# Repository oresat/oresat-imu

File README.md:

# oresat-imu
OreSat's IMU + Magnetometer board

CAN address: 0xh41

The IMU on the LV2 flight computer is the [ADIS16405](http://www.analog.com/en/products/sensors/inertial-measurement-units/adis16405.html#product-overview). The IMU contains a triaxial gyroscope, triaxial accelerometer, and an embedded temperature sensor. These parameters are output from the IMU via SPI, and will need to be sent to the CAN bus using an [STM32F042K6](http://www.st.com/content/st_com/en/products/microcontrollers/stm32-32-bit-arm-cortex-mcus/stm32f0-series/stm32f0x2/stm32f042k6.html) mcu or other M0 controller.

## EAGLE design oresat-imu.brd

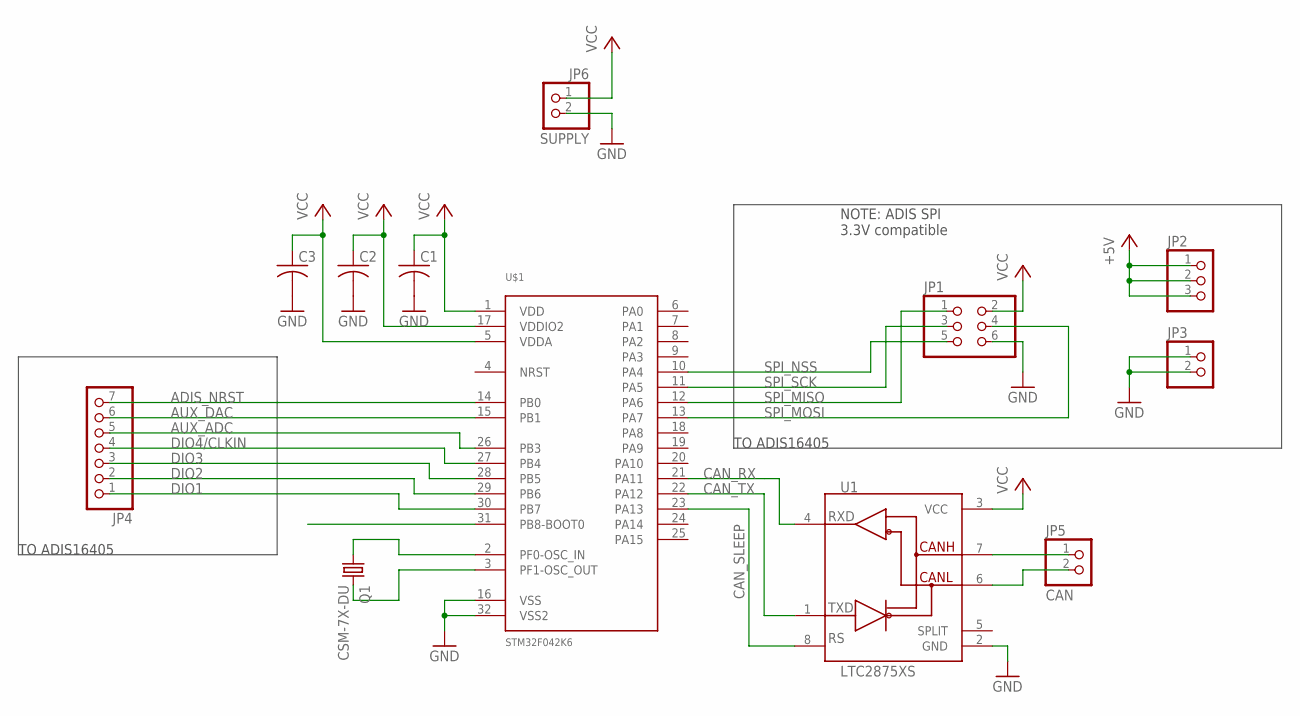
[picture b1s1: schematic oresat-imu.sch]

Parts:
C1, C2, C3: C-USC0805; C0805
JP1: PINHD-2X3; 2X03
JP2: PINHD-1X3; 1X03
JP3: PINHD-1X2; 1X02
JP4: PINHD-1X7; 1X07
JP5: CAN; 1X02
JP6: SUPPLY; 1X02/90
Q1: CSM-7X-DU
U1: LTC2875XS; SO-08
U$1: STM32F042K6; LQFP32-7X7

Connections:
+5V: JP2.1, JP2.2, JP2.3
ADIS_NRST: JP4.7, U$1.14 (PB0)
AUX_ADC: JP4.5, U$1.26 (PB3)
AUX_DAC: JP4.6, U$1.15 (PB1)
CANH: JP5.1, U1.7 (CANH)
CANL: JP5.2, U1.6 (CANL)
CAN_RX: U1.4 (RXD), U$1.21 (PA11)
CAN_SLEEP: U1.8 (RS1), U$1.23 (PA13)
CAN_TX: U1.1 (TXD), U$1.22 (PA12)
DIO1: JP4.1, U$1.30 (PB7)
DIO2: JP4.2, U$1.29 (PB6)
DIO3: JP4.3, U$1.28 (PB5)
DIO4/CLKIN: JP4.4, U$1.27 (PB4)
GND: C1.2, C2.2, C3.2, JP1.6, JP3.1, JP3.2, JP6.2, U1.2 (GND), U$1.16 (VSS), U$1.32 (VSS2)
unnamed: Q1.1, U$1.2 (PF0-OSC_IN)
unnamed: Q1.2, U$1.3 (PF1-OSC_OUT)
SPI_MISO: JP1.1, U$1.12 (PA6)
SPI_MOSI: JP1.4, U$1.13 (PA7)
SPI_NSS: JP1.5, U$1.10 (PA4)
SPI_SCK: JP1.3, U$1.11 (PA5)
VCC: C1.1, C2.1, C3.1, JP1.2, JP6.1, U1.3 (VCC), U$1.1 (VDD), U$1.5 (VDDA), U$1.17 (VDDIO2)

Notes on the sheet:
TO ADIS16405
NOTE: ADIS SPI 3.3V compatible

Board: 2 copper layers, 12 parts (0 on the bottom side), 21 nets, no tracks yet.

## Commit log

2017-06-27 Started PCB schematic
2017-06-28 named connections
2017-06-29 Added
2019-08-20 "auto-generated from update_repos.py"
